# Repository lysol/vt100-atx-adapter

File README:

VT100 ATX Adapter
-----------------

Like others with DEC VT10X terminals, the power supply board in mine
wasn't working. I've started off with bbenchoff's here:

https://github.com/bbenchoff/VT100Adapter

But the pinout is just flat wrong, at least for my VT105, and
according to the technical documentation for the VT100,
which is widely available on Bitsavers.

This version corrects the 12V/GND pin placement on the edge
connector (12V GND 12V GND, rather than 12V GND GND GND),
and uses a soon-to-be obsolete DC-DC converter
for converting +5V to negative voltages, specifically -24V,
which is in tolerance for the NVRAM for the VT10X terminals,
which is absolutely required for the self-check to even complete
on startup.

I've also corrected the edge trace pitch, as bbenchoff's,
while still functional, is slightly off and some of the pins
are close to the edge of the traces.

You could still use this board with a linear supply setup
if you can't source the NMT0572SC; you'll need to supply
your own step-down transformer and rectifier, but those
sorts of circuits are extremely simple and widely available
on the internet, and bbenchoff's adapter is a good reference
for such a design. The current draw of a VT100's -23V rail
is specified as 10mA, so you have a lot of rectifiers that
would work, not necessarily the one in the BOM for the other
adapter.

For now the NMT0572SC seems to be widely available, and a
convenient option.

For silly reasons I have a large rectangle on both F.MASK
and B.MASK, making it a solder mask-less board. Delete them
in KiCAD if you'd like a reasonable looking solder mask,
as I designed it with a normal solder mask to begin with.

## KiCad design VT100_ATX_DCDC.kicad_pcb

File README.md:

Warning: This part worked for me, but there may be variations in DEC VT100 terminals or
terminals based on the VT100 (like the VT105, which I have). I've attempted to accomodate
what differences I may have encountered in research but definitely consult your model's
documentation to ensure its compatibility before building one blindly
and frying your terminal.

VT100 ATX Adapter
-----------------

Like others with DEC VT10X terminals, the power supply board in mine
wasn't working. I've started off with bbenchoff's [here](https://github.com/bbenchoff/VT100Adapter),
but had to modify it to make it work with my VT105, which is essentially
a stock VT100 with Advanced Video and Waveform Graphics boards.

This version corrects the 12V/GND pin placement on the edge
connector (12V GND 12V GND, rather than 12V GND GND GND),
and uses an isolated DC-DC converter to generate -23 (well, -24) volts.
The VT100 Basic Video board uses the potential between +12V
and the -23V to generate the -35V supply for the ER1400
NVRAM. This is mostly possible because of the extremely low (10mA)
current maximum of the original -23V line, and the +/- 8%
tolerance of the -35V requirement for said IC.

I've also corrected the edge trace pitch, as bbenchoff's,
while still functional, is slightly off and some of the pins
are close to the edge of the traces.

* [Bill of Materials](VT100_ATX_DCDC.csv)
* [Schematic](VT100_ATX_DCDC.pdf)

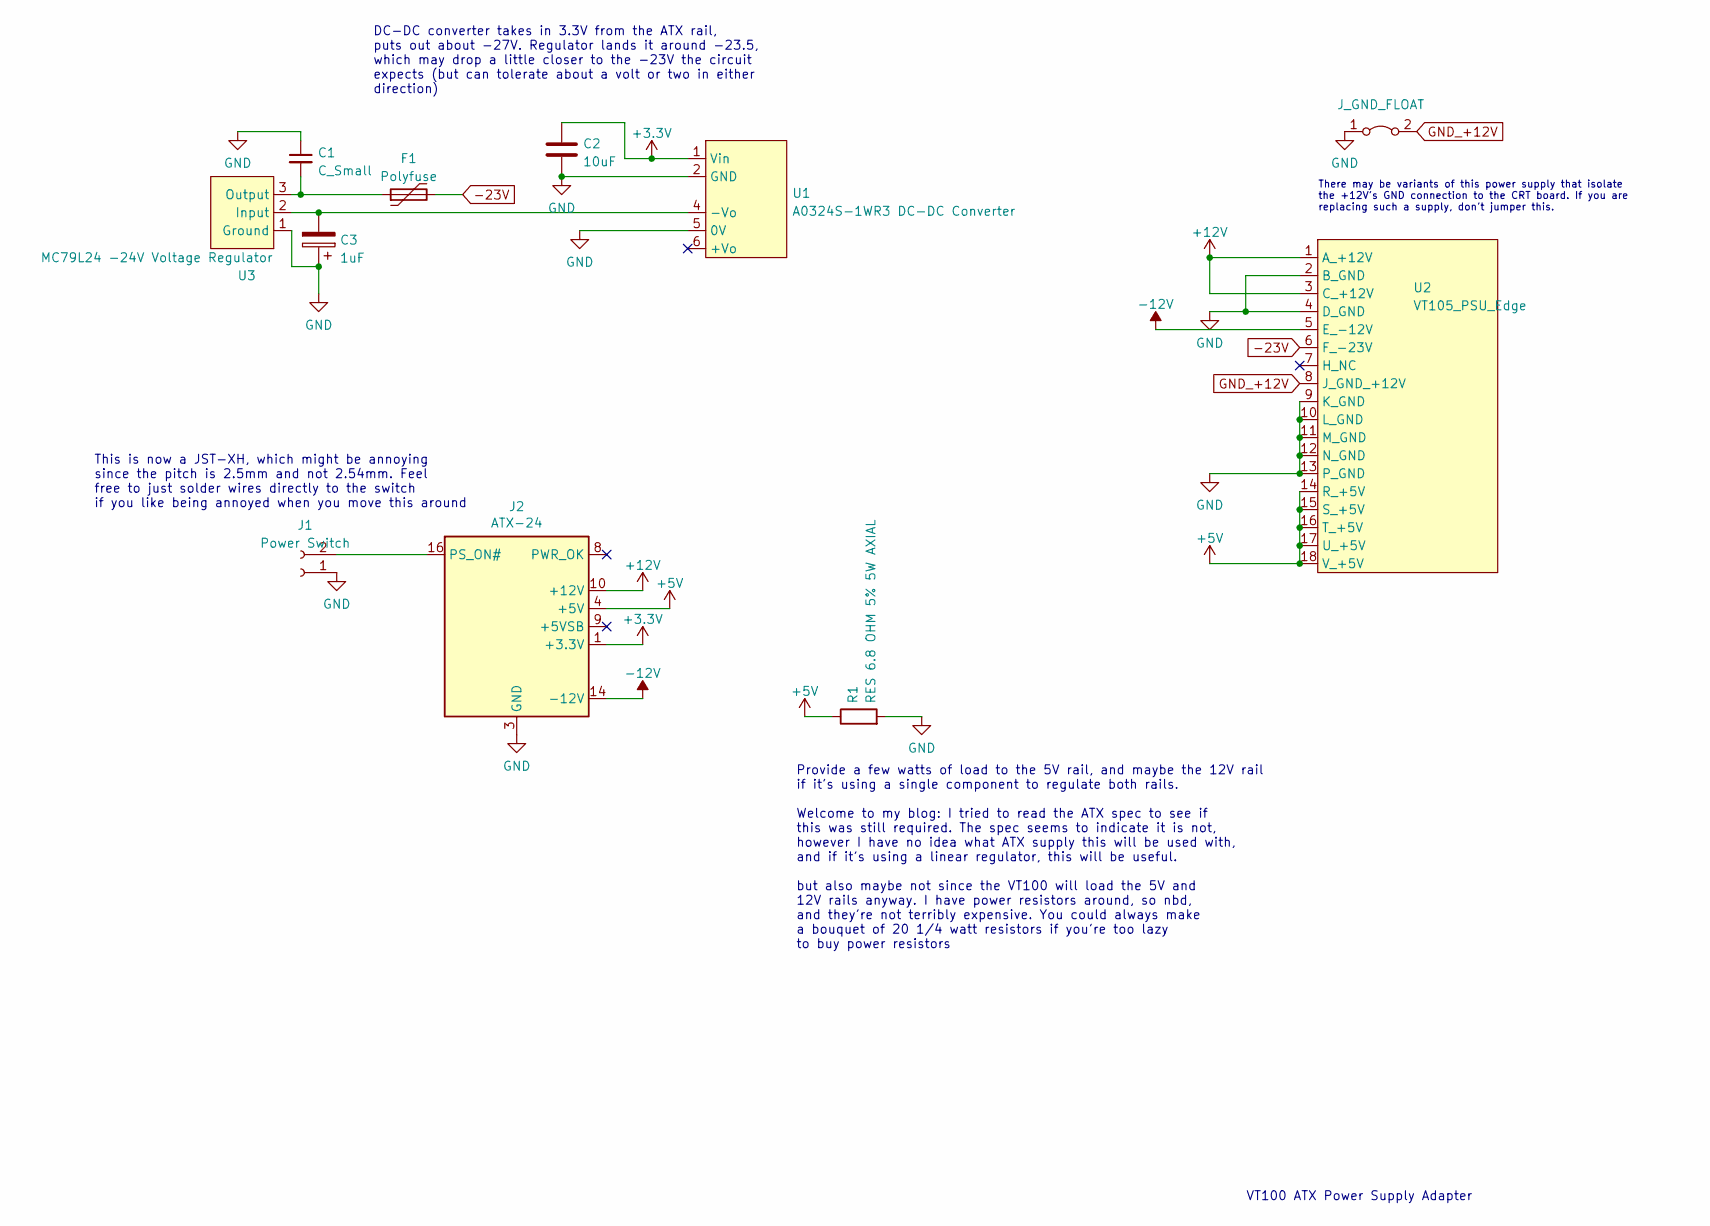
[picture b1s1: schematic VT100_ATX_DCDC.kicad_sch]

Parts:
C1: C_Small; C_Disc_D3.8mm_W2.6mm_P2.50mm; Part Number C315C104M5U5TA; Digi-Key Part Number 399-4151-ND
C2: 10uF; CP_Radial_D5.0mm_P2.00mm; Part Number 860010372001; Digi-Key Part Number 732-8593-1-ND
C3: 1uF; CP_Radial_D5.0mm_P2.00mm; Part Number 860020672005; Digi-Key Part Number 732-8851-1-ND
F1: Polyfuse; CMF-RL25U-0; Part Number CMF-RL25U-0; Digi-Key Part Number CMF-RL25U-0-ND
J1: Power Switch; JST_XH_B2B-XH-A_1x02_P2.50mm_Vertical; Part Number B2B-XH-A(LF)(SN); Digi-Key Part Number 455-2247-ND
J2: ATX-24; ATX24_RIGHT_ANGLE; Part Number 0039301240; Digi-Key Part Number WM1362-ND
JP1: J_GND_FLOAT; SolderJumper-2_P1.3mm_Bridged2Bar_Pad1.0x1.5mm
R1: RES 6.8 OHM 5% 5W AXIAL; ROX5SSJ6R8; Part Number ROX5SSJ6R8; Digi-Key Part Number A142748CT-ND
U1: A0324S-1WR3 DC-DC Converter; A0324S-1WR3‎; Part Number A0324S-1WR3; Digi-Key Part Number 2725-A0324S-1WR3-ND
U2: VT105_PSU_Edge; VT105_Card_Edge
U3: MC79L24 -24V Voltage Regulator; TO-92_Inline; Part Number MC79L24ABPG; Digi-Key Part Number MC79L24ABPG-ND

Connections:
+3.3V: C2.1, J2.1 (+3.3V), J2.2 (+3.3V), J2.12 (+3.3V), J2.13 (+3.3V), U1.1 (Vin)
+5V: J2.4 (+5V), J2.6 (+5V), J2.21 (+5V), J2.22 (+5V), J2.23 (+5V), R1.1, U2.14 (R_+5V), U2.15 (S_+5V), U2.16 (T_+5V), U2.17 (U_+5V), U2.18 (V_+5V)
+12V: J2.10 (+12V), J2.11 (+12V), U2.1 (A_+12V), U2.3 (C_+12V)
-12V: J2.14 (-12V), U2.5 (E_-12V)
-23V: F1.2, U2.6 (F_-23V)
GND: C1.1, C2.2, C3.1, J1.1, J2.3 (GND), J2.5 (GND), J2.7 (GND), J2.15 (GND), J2.17 (GND), J2.18 (GND), J2.19 (GND), J2.24 (GND), JP1.1 (A), R1.2, U1.2 (GND), U1.5 (0V), U2.2 (B_GND), U2.4 (D_GND), U2.9 (K_GND), U2.10 (L_GND), U2.11 (M_GND), U2.12 (N_GND), U2.13 (P_GND), U3.1 (Ground)
GND_+12V: JP1.2 (B), U2.8 (J_GND_+12V)
unnamed: C1.2, F1.1, U3.3 (Output)
unnamed: C3.2, U1.4 (-Vo), U3.2 (Input)
unnamed: J1.2, J2.16 (PS_ON#)

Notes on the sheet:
VT100 ATX Power Supply Adapter
This is now a JST-XH, which might be annoying since the pitch is 2.5mm and not 2.54mm. Feel free to just solder wires directly to the switch if you like being annoyed when you move this around
Provide a few watts of load to the 5V rail, and maybe the 12V rail if it's using a single component to regulate both rails. Welcome to my blog: I tried to read the ATX spec to see if this was still required. The spec seems to indicate it is not, however I have no idea what ATX supply this will be u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
There may be variants of this power supply that isolate the +12V's GND connection to the CRT board. If you are replacing such a supply, don't jumper this.
DC-DC converter takes in 3.3V from the ATX rail, puts out about -27V. Regulator lands it around -23.5, which may drop a little closer to the -23V the circuit expects (but can tolerate about a volt or two in either direction)

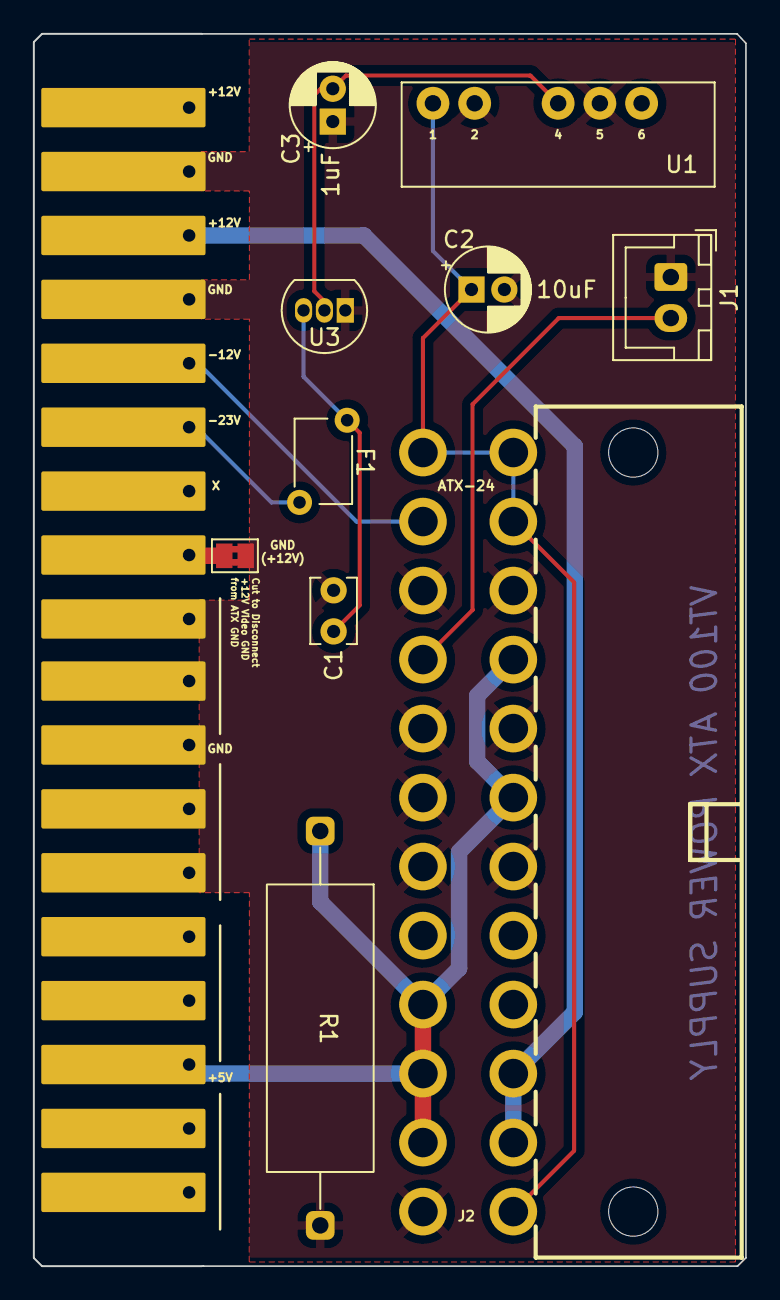
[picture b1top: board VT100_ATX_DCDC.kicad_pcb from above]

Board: 2 copper layers, 43.3 x 75.0 mm, 11 parts (0 on the bottom side), 10 nets.

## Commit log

2022-10-29 add readme
2022-10-29 reword and move to md
2022-10-29 made the entire board smaller, moved things around
    replaced the cap footprint with a smaller one, since
    you can get small-ish 1uf 50V caps this size easily
    made the power resistor vertical, it looks cool
    and saves space, which the VT100 has plenty of inside
    moved the 12V ground slice location to the back, why not
    grouped various things to make it easier to work on
2022-10-29 update adapter image
2022-10-29 add BOM
2022-10-30 fix link
2022-10-31 add bom fields
2022-10-31 replace DCDC converter with 555 negative supply circuit
2022-11-01 add warning
2022-11-02 use a different power module instead of my jank ass 555 circuit
2022-11-05 add voltage regulator for DC-DC converter
    the DC-DC converter came out to like -26.7V, that is too hot man
2022-11-06 make board a little roomier again, use different resistor
    I made a model for the new one in openscad because the mfg provided
    a model without bent leads for placement in a footprint. why
    would you think that is useful?
    I made it in openscad ok. converted to step using FreeCAD
2022-11-06 add schematic notes, export pdf
2022-11-06 add schematic link to readme
2022-11-10 update schematic after testing on the breadboard
2022-11-10 eliminate a via
2022-11-12 add polyfuse, add missing footprint
2022-11-12 make list
2022-11-15 adjust pitch of edge connector to match real edge socket
2022-12-20 remove jumper, not actually populated
2024-02-26 Update README.md
    Update warning to remove "in progress" remark.
2024-07-09 Delete VT100_ATX_DCDC.jpg
    outdated render
